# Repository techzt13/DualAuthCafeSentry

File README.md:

# Dual-Auth Cafe Sentry

**Hackathon build project — Sentry Pod + Pocket Keyfob**

The project is an access-control demonstrator with two hardware units:

- **Sentry Pod:** NFC credential reader, motion/tamper sensing, alarm output and local controls.
- **Pocket Keyfob:** user-held companion with a button and haptic feedback.

The intended deliverables are editable KiCad electronics projects, editable FreeCAD enclosure models, firmware, build documentation and a repeatable test plan. This repository is an engineering prototype workspace, not a released consumer product.

## Current design workspace

- [Sentry Pod KiCad project](hardware/sentry-pod/sentry-pod.kicad_pro)
- [Pod BQ25185 power-stage evaluation schematic](hardware/sentry-pod/pod-power-stage.kicad_sch)
- [Pod PAM8904E audio-stage evaluation schematic](hardware/sentry-pod/pod-audio-stage.kicad_sch)
- [Pocket Keyfob KiCad project](hardware/pocket-keyfob/pocket-keyfob.kicad_pro)
- [FreeCAD enclosure macro](cad/create_enclosures.FCMacro)
- [Mechanical model instructions](cad/README.md)
- [Hardware workspace guide](hardware/README.md)
- [Latest handoff / last work completed](LAST-WORKED-ON.md)

## Current status

Both devices have native KiCad schematic and PCB placement drafts. The Keyfob has a provisional C3-Zero module interface, motor low-side switch, flyback diode, local bypass capacitors, button interface and service UART nets. The Pod has its controller/NFC/IMU interface and wired NFC reset stage, plus separate standalone charger and audio evaluation schematics.

Both PCBs remain **unrouted**. The Pod power/audio sheets are not yet integrated as hierarchical sheets or placed on its PCB. Battery/charger pairings, processor-board USB power isolation, sounder drive waveform, and several physical component interfaces remain HOLD. The FreeCAD macro has not yet been run, so no generated FCStd/STEP/STL or fit validation is claimed.

## First local checks

From the repository root, run the dependency-free source sanity checker:

    python3 scripts/check_design_sources.py

This checks S-expression structure, PCB pad/net references, selected critical net assignments and duplicate identifiers. It is not a substitute for KiCad's native checks.

Open each KiCad project in KiCad and run:
1. Schematic ERC.
2. Update PCB from schematic and resolve discrepancies.
3. PCB DRC.
4. Inspect 3D view and footprint/connector clearances.

For CAD, follow cad/README.md, run the macro in FreeCAD, inspect the generated editable documents, and verify all component envelopes, USB access, antenna clearances, retention and assembly tolerances.

## Engineering status rules

- **DRAFT** means editable engineering work exists but may contain unresolved assumptions.
- **HOLD** means do not connect or energise that interface until its dependencies are reviewed.
- **VALIDATED** may only be used after the relevant tool/test has actually passed and its evidence is recorded.
- Never treat a paper datasheet screen as proof of acoustic, RF, thermal, battery, haptic or physical performance.
- Do not order boards or parts or initiate fabrication without explicit project-owner approval.

Read PROJECT_SPEC.md, AGENTS.md and LAST-WORKED-ON.md before continuing engineering work.

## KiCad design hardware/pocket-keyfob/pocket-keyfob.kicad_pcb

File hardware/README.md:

# Hardware design workspace

Status: **native KiCad schematic and PCB placement drafts exist for both devices; neither PCB is routed or fabrication-ready. Standalone Pod power/audio evaluation sheets exist. FreeCAD macro exists but has not been run.**

## Sentry Pod

Files:
- sentry-pod.kicad_pro
- sentry-pod.kicad_sch
- sentry-pod.kicad_pcb
- sentry-pod.kicad_sym
- sym-lib-table
- fp-lib-table
- footprints.pretty/
- interface-contract.md
- power-stage-review.md
- pod-power-stage.kicad_sch (standalone BQ25185 evaluation block)
- audio-stage-review.md
- pod-audio-stage.kicad_sch (standalone PAM8904E 1x evaluation block)
- packaging-review.md
- pcb-layout-review.md

Current schematic content:
- Waveshare ESP32-S3-Zero SKU 25081 P15 contact map.
- ELECHOUSE PN5321 MINI I2C host interface, active-low reset.
- Adafruit MPU-6050 breakout product 3886 six-pin header interface.
- Active-low failsafe button.
- Provisional MMBT3904 reset sink with 10 kΩ / 100 kΩ / 10 kΩ network.
- Optional 4.7 kΩ I2C pull-ups marked DNP; PN532 module-revision discrepancy documented.

Current PCB placements:
- Provisional S3-Zero 18-contact castellated footprint.
- Adafruit 3886 1x6 2.54 mm daughter-module footprint.
- PN532 host-interface 7-pad solder row.
- Q1 and R1/R2/R3 reset-stage placements.
- 49.5 x 28 mm board outline with S3 antenna relief notch.

Still missing from Pod PCB:
- Charger, battery connector/NTC, USB VBUS isolation and ideal-diode path.
- Piezo driver, transducer connector and acoustic circuitry.
- Button footprint, test points, complete routing, copper/return paths and antenna keepout rules.

Current Pod packaging-study envelope: 72 x 34 x 29 mm.

## Pocket Keyfob

Files:
- pocket-keyfob.kicad_pro
- pocket-keyfob.kicad_sch
- pocket-keyfob.kicad_pcb
- sym-lib-table
- fp-lib-table
- footprints.pretty/
- interface-contract.md
- pcb-layout-review.md
- packaging-review.md

Current schematic content:
- Waveshare ESP32-C3-Zero SKU 25452 evaluation controller.
- Protected battery ADC and conditioned charge-status interfaces (power holds remain unresolved).
- Service UART RX/TX mapped to C3 contacts 17/18 and matching PCB pads.
- Active-low button interface.
- IRLML6344 N-channel MOSFET low-side motor switch.
- 100 Ω gate resistor, 100 kΩ hardware-off pull-down.
- Nexperia PMEG2010AEB,115 SOD-523 flyback diode.
- 100 nF and 10 µF motor-rail decoupling.
- VCLP1020B002L is the preferred motor evaluation reference only; O-13 remains open and Precision Microdrives 308-100 is an alternate.

Current PCB placements:
- Provisional upright C3-Zero 2x9 castellated footprint.
- Motor-wire solder pads, MOSFET, diode, gate resistors and motor-rail capacitors.
- 37 x 25 mm carrier outline with antenna relief notch and 24 assigned pad-to-net connections.

Still missing from Keyfob PCB:
- Battery/charger, USB-C charging path, regulator/source isolation and ADC divider.
- Physical button, battery connector and final motor retention.
- Complete routing, copper/return paths, test points and antenna keepout rules.

Current Keyfob packaging-study envelope: 44 x 30 x 15.5 mm.

## Release status

- Both schematics and PCBs are editable drafts.
- Both PCBs remain unrouted.
- Footprints are provisional and require physical-part/source-drawing checks.
- No KiCad ERC/DRC, FreeCAD run, STEP/STL export, physical fit, RF, acoustic, battery or haptic validation is claimed.
- Keep LAST-WORKED-ON.md current after each meaningful change.

## Source sanity checker

From the repository root, run:

    python3 scripts/check_design_sources.py

This dependency-free script checks S-expression balance, PCB net references, duplicate identifiers and selected critical pad/net contracts. It does not replace KiCad ERC/DRC or physical validation.

## Power/audio integration status

The Pod BQ25185 and PAM8904E blocks are real, editable standalone KiCad schematic files. They remain isolated evaluation sheets, not hierarchical sheets in the main Pod schematic and not PCB placements. All their supply, battery, control and output rails remain HOLD.

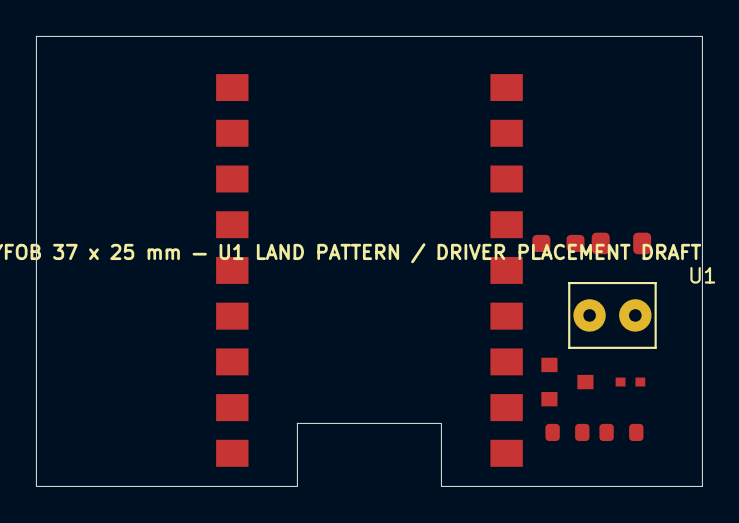
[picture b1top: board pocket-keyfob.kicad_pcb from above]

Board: 2 copper layers, 37.0 x 25.0 mm, 8 parts (0 on the bottom side), 5 nets, no tracks yet.

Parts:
C1: 100nF; C_0603_1608Metric
C2: 10uF; C_0805_2012Metric
D1: PMEG2010AEB,115; D_SOD-523
J1: VCLP1020B002L motor wire pads (evaluation candida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; MotorWirePads_2x
Q1: IRLML6344; SOT-23
R1: 100R; R_0603_1608Metric
R2: 100k; R_0603_1608Metric
U1: ESP32-C3-Zero SKU25452 — draft land pattern; C3Zero_Castellated_2x9

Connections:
K_3V3_MOTOR_HOLD: C1.1, C2.1, D1.1, J1.1
K_GND: C1.2, C2.2, Q1.2, R2.2, U1.2
K_MOTOR_GATE: Q1.1, R1.2, R2.1
K_MOTOR_PWM: R1.1, U1.7
K_MOTOR_SW: D1.2, J1.2, Q1.3

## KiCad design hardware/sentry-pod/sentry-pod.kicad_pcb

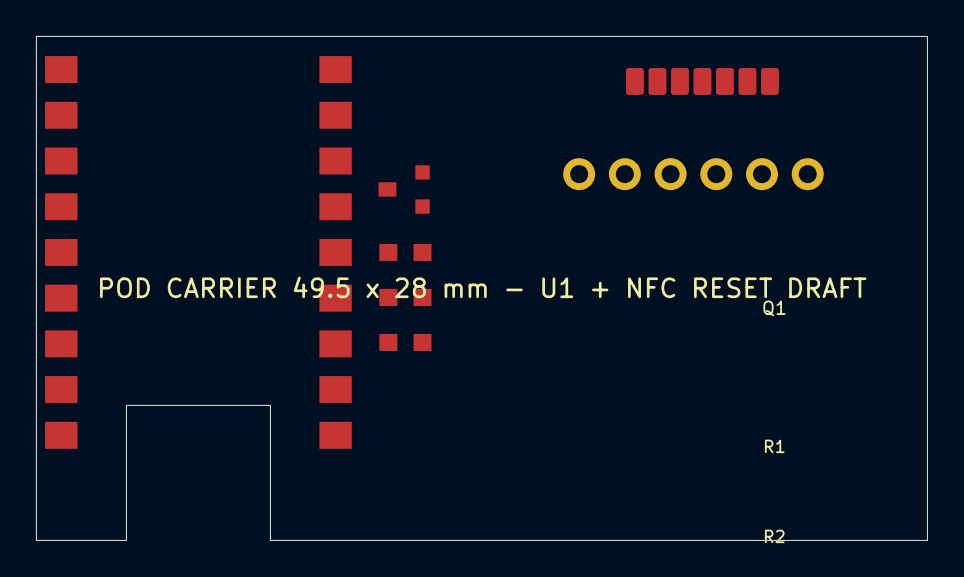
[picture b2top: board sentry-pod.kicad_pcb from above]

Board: 2 copper layers, 49.5 x 28.0 mm, 7 parts (0 on the bottom side), 8 nets, no tracks yet.

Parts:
J1: PN532 MX1.25 host wire pads; PN5321_MINI_Host_7Pad_Draft
J2: Adafruit 3886 / 1x6 2.54mm; Adafruit3886_Module_1x6
Q1: MMBT3904; MMBT3904_SOT23_Draft
R1, R2, R3: 0603; R_0603_Draft
U1: ESP32-S3-Zero / P15; S3Zero_Castellated_2x9

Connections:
GND: J1.GND, J2.3, Q1.2, R2.1, U1.17
P_3V3_PERIPH_HOLD: J1.VCC, J2.1, R3.1
P_I2C_SCL: J1.SCL, J2.4, U1.11
P_I2C_SDA: J1.SDA, J2.5, U1.12
P_IMU_INT: J2.6, U1.4
P_NFC_RESET_BASE: Q1.1, R1.2, R2.2
P_NFC_RESET_CTL: R1.1, U1.5
P_NFC_RESET_N: J1.RST, Q1.3, R3.2

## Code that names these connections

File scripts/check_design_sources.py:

#!/usr/bin/env python3
"""Dependency-free source sanity checks for the Dual-Auth Cafe Sentry KiCad drafts.

This is deliberately not a replacement for KiCad's parser, ERC, DRC, 3D viewer,
or a physical fit/electrical test. It checks S-expression structure, PCB net
references, duplicate UUID/reference identifiers, and a few project-critical
pad/net contracts so obvious text-edit regressions are caught early.
"""
from __future__ import annotations

import json
import re
import sys
from pathlib import Path

TOKEN = re.compile(r'"(?:\\.|[^"\\])*"|[()]|[^\s()]+')


class ParseError(ValueError):
    pass


def parse_sexpr(path: Path):
    text = path.read_text(encoding="utf-8")
    tokens = TOKEN.findall(text)
    pos = 0

    def parse_one():
        nonlocal pos
        if pos >= len(tokens):
            raise ParseError("unexpected end of file")
        token = tokens[pos]
        pos += 1
        if token != "(":
            if token == ")":
                raise ParseError("unexpected closing parenthesis")
            return json.loads(token) if token.startswith('"') else token
        result = []
        while True:
            if pos >= len(tokens):
                raise ParseError("unclosed list")
            if tokens[pos] == ")":
                pos += 1
                return result
            result.append(parse_one())

    root = parse_one()
    if pos != len(tokens):
        raise ParseError("trailing tokens after root expression")
    if not isinstance(root, list):
        raise ParseError("root is not a list")
    return root


def walk(node):
    if isinstance(node, list):
        yield node
        for child in node:
            yield from walk(child)


def child(node, name):
    for item in node:
        if isinstance(item, list) and item and item[0] == name:
            return item
    return None


def children(node, name):
    return [item for item in node if isinstance(item, list) and item and item[0] == name]


def property_value(node, key):
    for item in children(node, "property"):
        if len(item) >= 3 and item[1] == key:
            return item[2]
    return None


def fail(message):
    raise RuntimeError(message)


def check_file_structure(files):
    for path in files:
        root = parse_sexpr(path)
        uuids = [n[1] for n in walk(root) if n and n[0] == "uuid" and len(n) > 1]
        duplicates = sorted({u for u in uuids if uuids.count(u) > 1})
        if duplicates:
            fail(f"{path}: duplicate UUID(s): {', '.join(duplicates)}")
        print(f"PASS structure: {path}")


def check_pcb(path):
    root = parse_sexpr(path)
    nets = {}
    for item in children(root, "net"):
        if len(item) >= 3:
            net_id, name = int(item[1]), item[2]
            if net_id in nets:
                fail(f"{path}: duplicate net id {net_id}")
            nets[net_id] = name

    refs = {}
    pad_count = 0
    assigned_count = 0
    footprints = children(root, "footprint")
    for fp in footprints:
        ref = property_value(fp, "Reference")
        if ref:
            if ref in refs:
                fail(f"{path}: duplicate footprint reference {ref}")
            refs[ref] = fp
        for pad in children(fp, "pad"):
            pad_count += 1
            net = child(pad, "net")
            if not net:
                continue
            net_id = int(net[1])
            net_name = net[2]
            if net_id not in nets:
                fail(f"{path}: pad {ref or '?'}:{pad[1]} uses undefined net id {net_id}")
            if nets[net_id] != net_name:
                fail(f"{path}: pad {ref or '?'}:{pad[1]} net name/id mismatch")
            if net_id != 0:
                assigned_count += 1
    print(f"PASS PCB nets: {path} — {len(nets)-1} named nets, {assigned_count}/{pad_count} assigned pads, {len(footprints)} footprints")
    return refs


def pad_net(fp, pad_number):
    for pad in children(fp, "pad"):
        if len(pad) > 1 and pad[1] == str(pad_number):
            net = child(pad, "net")
            return net[2] if net else ""
    return None


def check_project_contracts(repo):
    key_sch = parse_sexpr(repo / "hardware/pocket-keyfob/pocket-keyfob.kicad_sch")
    labels = {n[1] for n in walk(key_sch) if n and n[0] in ("label", "global_label", "hierarchical_label") and len(n) > 1}
    for label in ("K_UART_RX", "K_UART_TX", "K_MOTOR_PWM", "K_MOTOR_GATE", "K_MOTOR_SW"):
        if label not in labels:
            fail(f"Keyfob schematic is missing label {label}")

    key_refs = check_pcb(repo / "hardware/pocket-keyfob/pocket-keyfob.kicad_pcb")
    expected = {
        ("U1", "17"): "K_UART_RX",
        ("U1", "18"): "K_UART_TX",
        ("J1", "1"): "K_3V3_MOTOR_HOLD",
        ("J1", "2"): "K_MOTOR_SW",
        ("Q1", "1"): "K_MOTOR_GATE",
        ("Q1", "2"): "K_GND",
        ("Q1", "3"): "K_MOTOR_SW",
        ("D1", "1"): "K_3V3_MOTOR_HOLD",
        ("D1", "2"): "K_MOTOR_SW",
    }
    for (ref, pad), expected_net in expected.items():
        if ref not in key_refs:
            fail(f"Keyfob PCB is missing footprint {ref}")
        actual = pad_net(key_refs[ref], pad)
        if actual != expected_net:
            fail(f"Keyfob PCB {ref}.{pad}: expected {expected_net}, got {actual}")

    pod_refs = check_pcb(repo / "hardware/sentry-pod/sentry-pod.kicad_pcb")
    pod_expected = {
        ("Q1", "1"): "P_NFC_RESET_BASE",
        ("Q1", "2"): "GND",
        ("Q1", "3"): "P_NFC_RESET_N",
        ("R1", "1"): "P_NFC_RESET_CTL",
        ("R1", "2"): "P_NFC_RESET_BASE",
        ("R2", "1"): "GND",
        ("R2", "2"): "P_NFC_RESET_BASE",
        ("R3", "1"): "P_3V3_PERIPH_HOLD",
        ("R3", "2"): "P_NFC_RESET_N",
    }
    for (ref, pad), expected_net in pod_expected.items():
        if ref not in pod_refs:
            fail(f"Pod PCB is missing footprint {ref}")
        actual = pad_net(pod_refs[ref], pad)
        if actual != expected_net:
            fail(f"Pod PCB {ref}.{pad}: expected {expected_net}, got {actual}")
    print("PASS project contracts: Keyfob UART/motor stage and Pod NFC reset pad mappings")


def main():
    repo = Path(__file__).resolve().parents[1]
    files = sorted((repo / "hardware").rglob("*.kicad_sch"))
    files += sorted((repo / "hardware").rglob("*.kicad_pcb"))
    files += sorted((repo / "hardware").rglob("*.kicad_mod"))
    if not files:
        fail("no KiCad source files found")
    check_file_structure(files)
    check_project_contracts(repo)
    print("\nSource checks passed. This does NOT mean KiCad ERC/DRC or fabrication checks passed.")


if __name__ == "__main__":
    try:
        main()
    except Exception as exc:
        print(f"FAIL: {exc}", file=sys.stderr)
        sys.exit(1)
